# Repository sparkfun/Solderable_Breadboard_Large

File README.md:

#Solderable Breadboard Large
---

Solderable breadboard that mirrors a large (63 column) solderless board.

Includes provisions for screw terminal connectors, and an trace down the center gutter for ground.  Can be configured for up to 5 independent power rails.

[  
*Solderable Breadboard Large*](https://www.sparkfun.com/products/12699)

Design files for the [Solderable Breadboard Large](https://www.sparkfun.com/products/12699).

Repository Contents
-------------------

* **/Hardware** - Eagle PCB and schematic files

License Information
-------------------
The hardware is released under [Creative Commons ShareAlike 4.0 International](https://creativecommons.org/licenses/by-sa/4.0/).
The code is beerware; if you see me (or any other SparkFun employee) at the local, and you've found our code helpful, please buy us a round!

Distributed as-is; no warranty is given.

Author: Byron Jacquot @ SparkFun Electonics

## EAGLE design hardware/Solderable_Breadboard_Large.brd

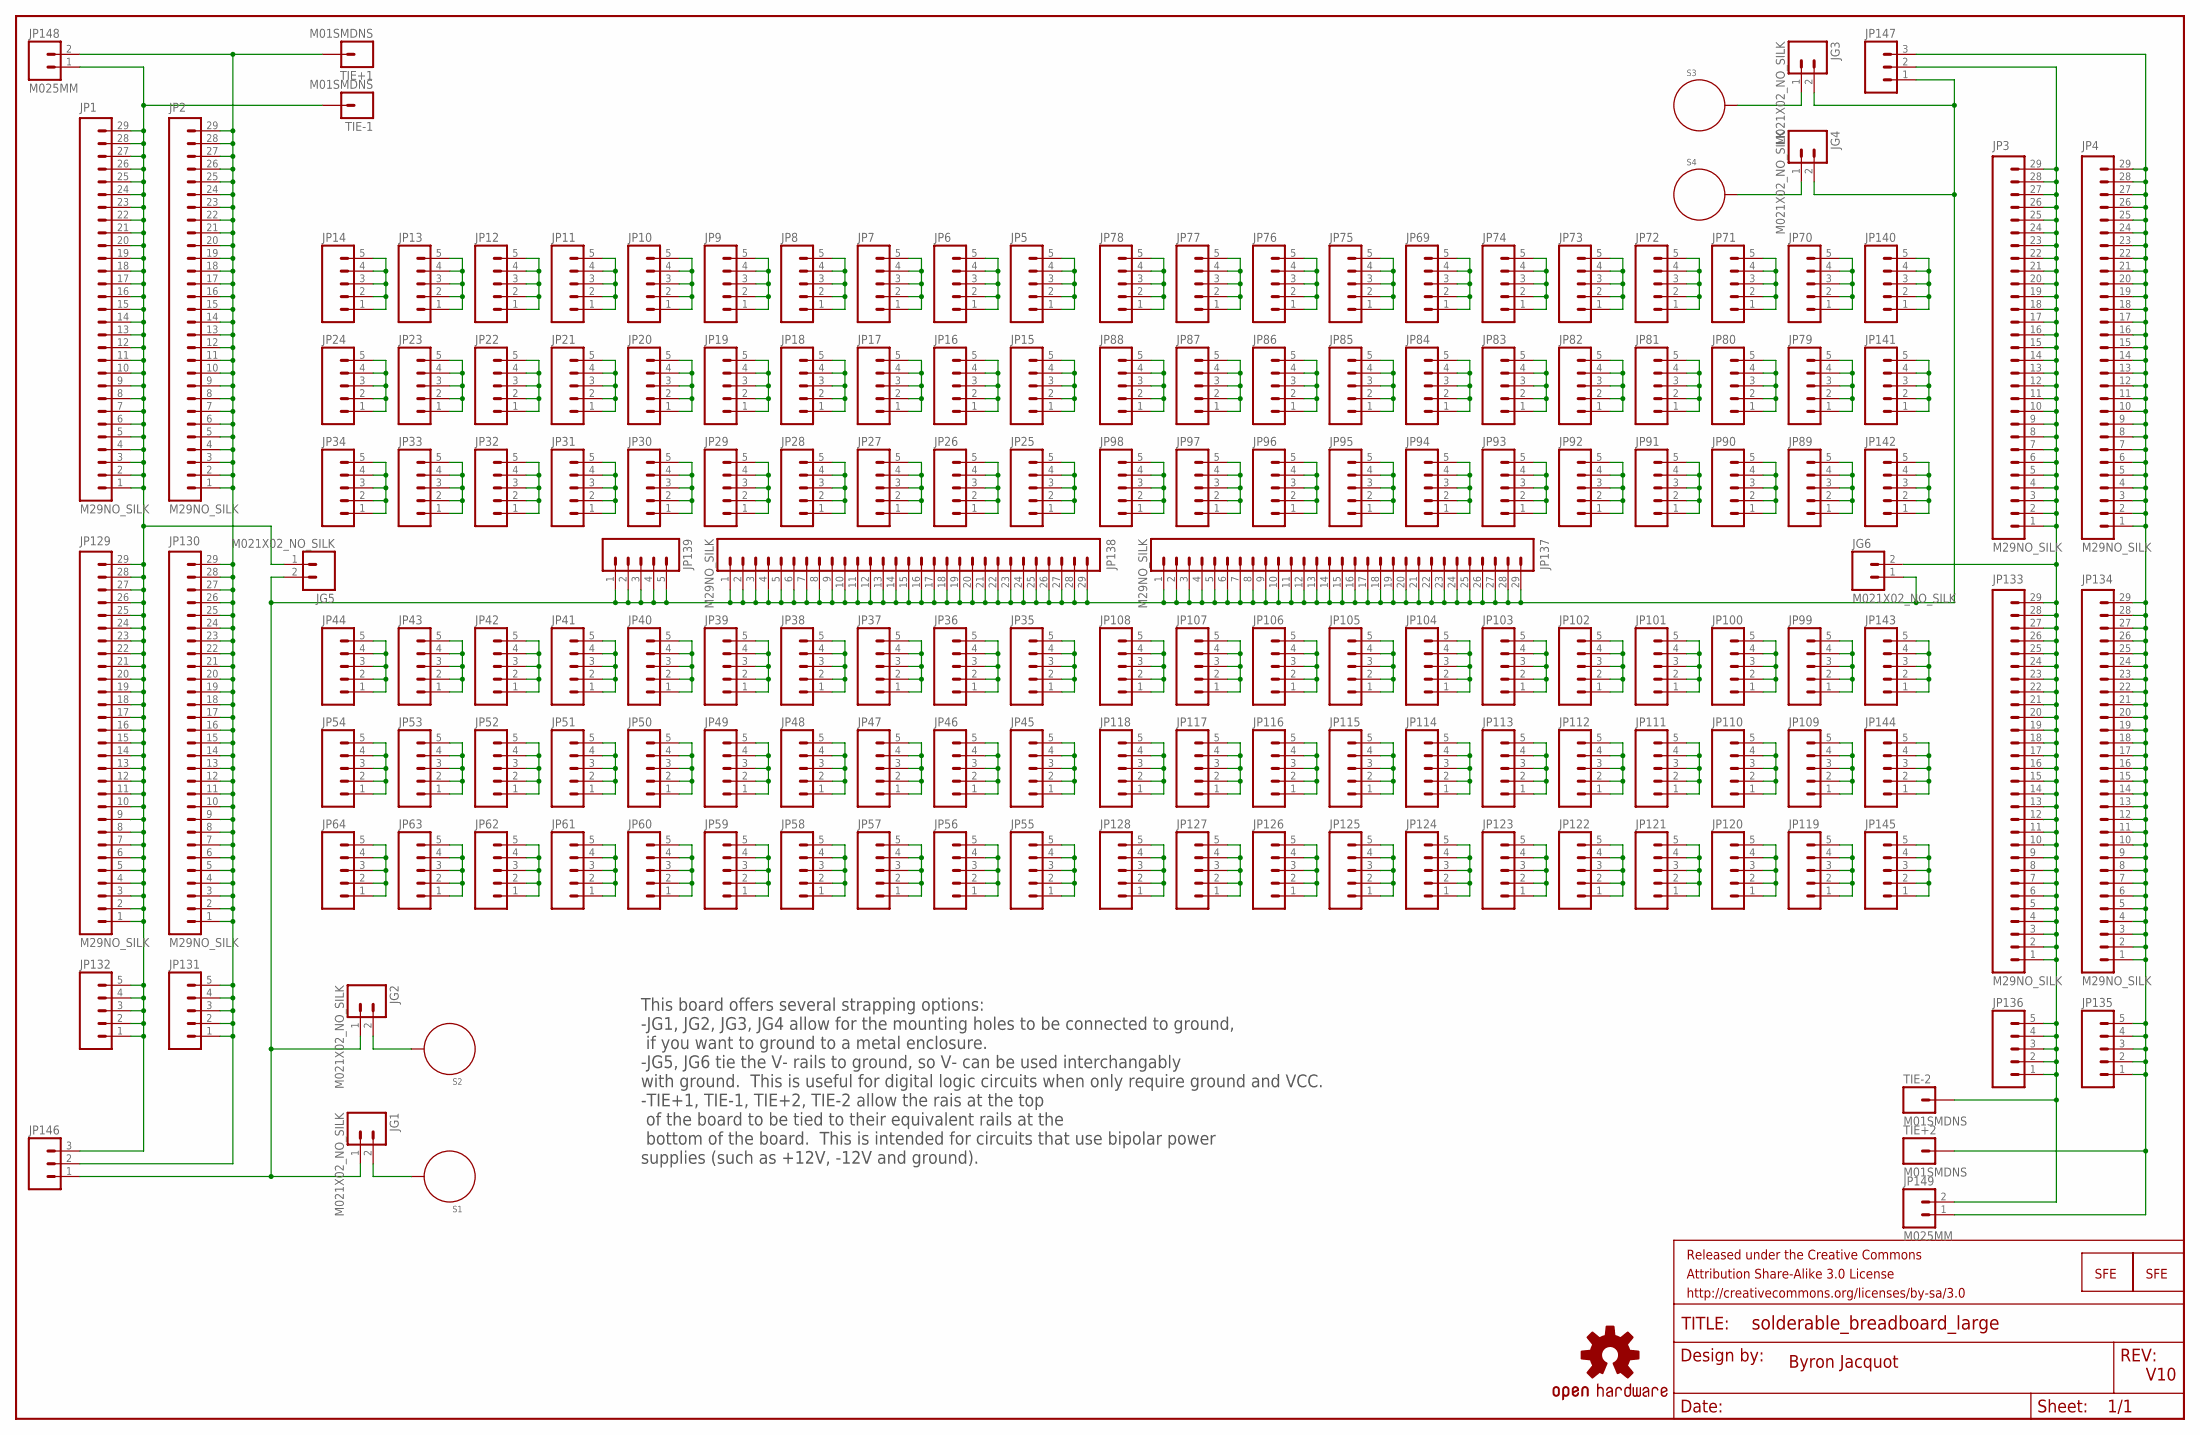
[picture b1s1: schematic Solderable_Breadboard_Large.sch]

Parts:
FRAME2: FRAME-LEDGER; CREATIVE_COMMONS
JG1, JG2, JG3, JG4, JG5, JG6: M021X02_NO_SILK; 1X02_NO_SILK
JP1, JP2, JP3, JP4, JP129, JP130, JP133, JP134, JP137, JP138: M29NO_SILK; 1X29_NO_SILK
JP5, JP6, JP7, JP8, JP9, JP10, JP11, JP12, JP13, JP14, JP15, JP16, JP17, JP18, JP19, JP20, JP21, JP22, JP23, JP24, JP25, JP26, JP27, JP28, JP29, JP30, JP31, JP32, JP33, JP34, JP35, JP36, JP37, JP38, JP39, JP40, JP41, JP42, JP43, JP44, JP45, JP46, JP47, JP48, JP49, JP50, JP51, JP52, JP53, JP54, JP55, JP56, JP57, JP58, JP59, JP60, JP61, JP62, JP63, JP64, JP69, JP70, JP71, JP72, JP73, JP74, JP75, JP76, JP77, JP78, JP79, JP80, JP81, JP82, JP83, JP84, JP85, JP86, JP87, JP88, JP89, JP90, JP91, JP92, JP93, JP94, JP95, JP96, JP97, JP98, JP99, JP100, JP101, JP102, JP103, JP104, JP105, JP106, JP107, JP108, JP109, JP110, JP111, JP112, JP113, JP114, JP115, JP116, JP117, JP118, JP119, JP120, JP121, JP122, JP123, JP124, JP125, JP126, JP127, JP128, JP131, JP132, JP135, JP136, JP139, JP140, JP141, JP142, JP143, JP144, JP145: M05NO_SILK; 1X05_NO_SILK
JP146, JP147: M03-SCREW-5MM; SCREWTERMINAL-5MM-3
JP148, JP149: M025MM; SCREWTERMINAL-5MM-2
LOGO1, LOGO2: LOGO-SFENEW; SFE-NEW-WEBLOGO
LOGO3: OSHW-LOGOS; OSHW-LOGO-S
S1, S2, S3, S4: STANDOFF_ELECTRICAL; STANDOFF-ELECTRICAL
TIE+1, TIE+2: M01SMDNS; 1X01NS
TIE-1, TIE-2: M01SMDNS; 1X01NS

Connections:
GND: JG1.1, JG2.1, JG3.2, JG4.2, JG5.2, JG6.1, JP137.1, JP137.2, JP137.3, JP137.4, JP137.5, JP137.6, JP137.7, JP137.8, JP137.9, JP137.10, JP137.11, JP137.12, JP137.13, JP137.14, JP137.15, JP137.16, JP137.17, JP137.18, JP137.19, JP137.20, JP137.21, JP137.22, JP137.23, JP137.24, JP137.25, JP137.26, JP137.27, JP137.28, JP137.29, JP138.1, JP138.2, JP138.3, JP138.4, JP138.5, JP138.6, JP138.7, JP138.8, JP138.9, JP138.10, JP138.11, JP138.12, JP138.13, JP138.14, JP138.15, JP138.16, JP138.17, JP138.18, JP138.19, JP138.20, JP138.21, JP138.22, JP138.23, JP138.24, JP138.25, JP138.26, JP138.27, JP138.28, JP138.29, JP139.1, JP139.2, JP139.3, JP139.4, JP139.5, JP146.1, JP147.1
unnamed: JG1.2, S1.P1
unnamed: JG2.2, S2.P1
unnamed: JP10.1, JP10.2, JP10.3, JP10.4, JP10.5
unnamed: JP5.1, JP5.2, JP5.3, JP5.4, JP5.5
unnamed: JP6.1, JP6.2, JP6.3, JP6.4, JP6.5
unnamed: JP7.1, JP7.2, JP7.3, JP7.4, JP7.5
unnamed: JP8.1, JP8.2, JP8.3, JP8.4, JP8.5
unnamed: JP9.1, JP9.2, JP9.3, JP9.4, JP9.5
unnamed: JP11.1, JP11.2, JP11.3, JP11.4, JP11.5
unnamed: JP12.1, JP12.2, JP12.3, JP12.4, JP12.5
unnamed: JP13.1, JP13.2, JP13.3, JP13.4, JP13.5
unnamed: JP14.1, JP14.2, JP14.3, JP14.4, JP14.5
unnamed: JP15.1, JP15.2, JP15.3, JP15.4, JP15.5
unnamed: JP16.1, JP16.2, JP16.3, JP16.4, JP16.5
unnamed: JP17.1, JP17.2, JP17.3, JP17.4, JP17.5
unnamed: JP18.1, JP18.2, JP18.3, JP18.4, JP18.5
unnamed: JP19.1, JP19.2, JP19.3, JP19.4, JP19.5
unnamed: JP20.1, JP20.2, JP20.3, JP20.4, JP20.5
unnamed: JP21.1, JP21.2, JP21.3, JP21.4, JP21.5
unnamed: JP22.1, JP22.2, JP22.3, JP22.4, JP22.5
unnamed: JP23.1, JP23.2, JP23.3, JP23.4, JP23.5
unnamed: JP24.1, JP24.2, JP24.3, JP24.4, JP24.5
unnamed: JP25.1, JP25.2, JP25.3, JP25.4, JP25.5
unnamed: JP26.1, JP26.2, JP26.3, JP26.4, JP26.5
unnamed: JP27.1, JP27.2, JP27.3, JP27.4, JP27.5
unnamed: JP28.1, JP28.2, JP28.3, JP28.4, JP28.5
unnamed: JP29.1, JP29.2, JP29.3, JP29.4, JP29.5
unnamed: JP30.1, JP30.2, JP30.3, JP30.4, JP30.5
unnamed: JP31.1, JP31.2, JP31.3, JP31.4, JP31.5
unnamed: JP32.1, JP32.2, JP32.3, JP32.4, JP32.5
unnamed: JP33.1, JP33.2, JP33.3, JP33.4, JP33.5
unnamed: JP34.1, JP34.2, JP34.3, JP34.4, JP34.5
unnamed: JP35.1, JP35.2, JP35.3, JP35.4, JP35.5
unnamed: JP36.1, JP36.2, JP36.3, JP36.4, JP36.5
unnamed: JP37.1, JP37.2, JP37.3, JP37.4, JP37.5
unnamed: JP38.1, JP38.2, JP38.3, JP38.4, JP38.5
unnamed: JP39.1, JP39.2, JP39.3, JP39.4, JP39.5
unnamed: JP40.1, JP40.2, JP40.3, JP40.4, JP40.5
unnamed: JP41.1, JP41.2, JP41.3, JP41.4, JP41.5
unnamed: JP42.1, JP42.2, JP42.3, JP42.4, JP42.5
unnamed: JP43.1, JP43.2, JP43.3, JP43.4, JP43.5
unnamed: JP44.1, JP44.2, JP44.3, JP44.4, JP44.5
unnamed: JP45.1, JP45.2, JP45.3, JP45.4, JP45.5
unnamed: JP46.1, JP46.2, JP46.3, JP46.4, JP46.5
unnamed: JP47.1, JP47.2, JP47.3, JP47.4, JP47.5
unnamed: JP48.1, JP48.2, JP48.3, JP48.4, JP48.5
unnamed: JP49.1, JP49.2, JP49.3, JP49.4, JP49.5
unnamed: JP50.1, JP50.2, JP50.3, JP50.4, JP50.5
unnamed: JP51.1, JP51.2, JP51.3, JP51.4, JP51.5
unnamed: JP52.1, JP52.2, JP52.3, JP52.4, JP52.5
unnamed: JP53.1, JP53.2, JP53.3, JP53.4, JP53.5
unnamed: JP54.1, JP54.2, JP54.3, JP54.4, JP54.5
unnamed: JP55.1, JP55.2, JP55.3, JP55.4, JP55.5
unnamed: JP56.1, JP56.2, JP56.3, JP56.4, JP56.5
unnamed: JP57.1, JP57.2, JP57.3, JP57.4, JP57.5
unnamed: JP58.1, JP58.2, JP58.3, JP58.4, JP58.5
unnamed: JP59.1, JP59.2, JP59.3, JP59.4, JP59.5
unnamed: JP60.1, JP60.2, JP60.3, JP60.4, JP60.5
unnamed: JP61.1, JP61.2, JP61.3, JP61.4, JP61.5
unnamed: JP62.1, JP62.2, JP62.3, JP62.4, JP62.5
unnamed: JP63.1, JP63.2, JP63.3, JP63.4, JP63.5
unnamed: JP64.1, JP64.2, JP64.3, JP64.4, JP64.5
unnamed: JG3.1, S3.P1
unnamed: JG4.1, S4.P1
unnamed: JP69.1, JP69.2, JP69.3, JP69.4, JP69.5
unnamed: JP70.1, JP70.2, JP70.3, JP70.4, JP70.5
unnamed: JP71.1, JP71.2, JP71.3, JP71.4, JP71.5
unnamed: JP72.1, JP72.2, JP72.3, JP72.4, JP72.5
unnamed: JP73.1, JP73.2, JP73.3, JP73.4, JP73.5
unnamed: JP74.1, JP74.2, JP74.3, JP74.4, JP74.5
unnamed: JP75.1, JP75.2, JP75.3, JP75.4, JP75.5
unnamed: JP76.1, JP76.2, JP76.3, JP76.4, JP76.5
unnamed: JP77.1, JP77.2, JP77.3, JP77.4, JP77.5
unnamed: JP78.1, JP78.2, JP78.3, JP78.4, JP78.5
unnamed: JP79.1, JP79.2, JP79.3, JP79.4, JP79.5
unnamed: JP80.1, JP80.2, JP80.3, JP80.4, JP80.5
unnamed: JP81.1, JP81.2, JP81.3, JP81.4, JP81.5
unnamed: JP82.1, JP82.2, JP82.3, JP82.4, JP82.5
unnamed: JP83.1, JP83.2, JP83.3, JP83.4, JP83.5
unnamed: JP84.1, JP84.2, JP84.3, JP84.4, JP84.5
unnamed: JP85.1, JP85.2, JP85.3, JP85.4, JP85.5
unnamed: JP86.1, JP86.2, JP86.3, JP86.4, JP86.5
unnamed: JP87.1, JP87.2, JP87.3, JP87.4, JP87.5
unnamed: JP88.1, JP88.2, JP88.3, JP88.4, JP88.5
unnamed: JP89.1, JP89.2, JP89.3, JP89.4, JP89.5
unnamed: JP90.1, JP90.2, JP90.3, JP90.4, JP90.5
unnamed: JP91.1, JP91.2, JP91.3, JP91.4, JP91.5
unnamed: JP92.1, JP92.2, JP92.3, JP92.4, JP92.5
unnamed: JP93.1, JP93.2, JP93.3, JP93.4, JP93.5
unnamed: JP94.1, JP94.2, JP94.3, JP94.4, JP94.5
unnamed: JP95.1, JP95.2, JP95.3, JP95.4, JP95.5
unnamed: JP96.1, JP96.2, JP96.3, JP96.4, JP96.5
unnamed: JP97.1, JP97.2, JP97.3, JP97.4, JP97.5
unnamed: JP98.1, JP98.2, JP98.3, JP98.4, JP98.5
unnamed: JP99.1, JP99.2, JP99.3, JP99.4, JP99.5
unnamed: JP100.1, JP100.2, JP100.3, JP100.4, JP100.5
unnamed: JP101.1, JP101.2, JP101.3, JP101.4, JP101.5
unnamed: JP102.1, JP102.2, JP102.3, JP102.4, JP102.5
unnamed: JP103.1, JP103.2, JP103.3, JP103.4, JP103.5
unnamed: JP104.1, JP104.2, JP104.3, JP104.4, JP104.5
unnamed: JP105.1, JP105.2, JP105.3, JP105.4, JP105.5
unnamed: JP106.1, JP106.2, JP106.3, JP106.4, JP106.5
unnamed: JP107.1, JP107.2, JP107.3, JP107.4, JP107.5
unnamed: JP108.1, JP108.2, JP108.3, JP108.4, JP108.5
unnamed: JP109.1, JP109.2, JP109.3, JP109.4, JP109.5
unnamed: JP110.1, JP110.2, JP110.3, JP110.4, JP110.5
unnamed: JP111.1, JP111.2, JP111.3, JP111.4, JP111.5
unnamed: JP112.1, JP112.2, JP112.3, JP112.4, JP112.5
unnamed: JP113.1, JP113.2, JP113.3, JP113.4, JP113.5
unnamed: JP114.1, JP114.2, JP114.3, JP114.4, JP114.5
unnamed: JP115.1, JP115.2, JP115.3, JP115.4, JP115.5
unnamed: JP116.1, JP116.2, JP116.3, JP116.4, JP116.5
unnamed: JP117.1, JP117.2, JP117.3, JP117.4, JP117.5
unnamed: JP118.1, JP118.2, JP118.3, JP118.4, JP118.5
unnamed: JP119.1, JP119.2, JP119.3, JP119.4, JP119.5
unnamed: JP120.1, JP120.2, JP120.3, JP120.4, JP120.5
unnamed: JP121.1, JP121.2, JP121.3, JP121.4, JP121.5
unnamed: JP122.1, JP122.2, JP122.3, JP122.4, JP122.5
unnamed: JP123.1, JP123.2, JP123.3, JP123.4, JP123.5
unnamed: JP124.1, JP124.2, JP124.3, JP124.4, JP124.5
unnamed: JP125.1, JP125.2, JP125.3, JP125.4, JP125.5
unnamed: JP126.1, JP126.2, JP126.3, JP126.4, JP126.5
unnamed: JP127.1, JP127.2, JP127.3, JP127.4, JP127.5
unnamed: JP128.1, JP128.2, JP128.3, JP128.4, JP128.5
unnamed: JP140.1, JP140.2, JP140.3, JP140.4, JP140.5
unnamed: JP141.1, JP141.2, JP141.3, JP141.4, JP141.5
unnamed: JP142.1, JP142.2, JP142.3, JP142.4, JP142.5
unnamed: JP143.1, JP143.2, JP143.3, JP143.4, JP143.5
unnamed: JP144.1, JP144.2, JP144.3, JP144.4, JP144.5
unnamed: JP145.1, JP145.2, JP145.3, JP145.4, JP145.5
V+BOT: JP4.1, JP4.2, JP4.3, JP4.4, JP4.5, JP4.6, JP4.7, JP4.8, JP4.9, JP4.10, JP4.11, JP4.12, JP4.13, JP4.14, JP4.15, JP4.16, JP4.17, JP4.18, JP4.19, JP4.20, JP4.21, JP4.22, JP4.23, JP4.24, JP4.25, JP4.26, JP4.27, JP4.28, JP4.29, JP134.1, JP134.2, JP134.3, JP134.4, JP134.5, JP134.6, JP134.7, JP134.8, JP134.9, JP134.10, JP134.11, JP134.12, JP134.13, JP134.14, JP134.15, JP134.16, JP134.17, JP134.18, JP134.19, JP134.20, JP134.21, JP134.22, JP134.23, JP134.24, JP134.25, JP134.26, JP134.27, JP134.28, JP134.29, JP135.1, JP135.2, JP135.3, JP135.4, JP135.5, JP147.3, JP149.1, TIE+2.1
V+TOP: JP2.1, JP2.2, JP2.3, JP2.4, JP2.5, JP2.6, JP2.7, JP2.8, JP2.9, JP2.10, JP2.11, JP2.12, JP2.13, JP2.14, JP2.15, JP2.16, JP2.17, JP2.18, JP2.19, JP2.20, JP2.21, JP2.22, JP2.23, JP2.24, JP2.25, JP2.26, JP2.27, JP2.28, JP2.29, JP130.1, JP130.2, JP130.3, JP130.4, JP130.5, JP130.6, JP130.7, JP130.8, JP130.9, JP130.10, JP130.11, JP130.12, JP130.13, JP130.14, JP130.15, JP130.16, JP130.17, JP130.18, JP130.19, JP130.20, JP130.21, JP130.22, JP130.23, JP130.24, JP130.25, JP130.26, JP130.27, JP130.28, JP130.29, JP131.1, JP131.2, JP131.3, JP131.4, JP131.5, JP146.2, JP148.2, TIE+1.1
V-BOT: JG6.2, JP3.1, JP3.2, JP3.3, JP3.4, JP3.5, JP3.6, JP3.7, JP3.8, JP3.9, JP3.10, JP3.11, JP3.12, JP3.13, JP3.14, JP3.15, JP3.16, JP3.17, JP3.18, JP3.19, JP3.20, JP3.21, JP3.22, JP3.23, JP3.24, JP3.25, JP3.26, JP3.27, JP3.28, JP3.29, JP133.1, JP133.2, JP133.3, JP133.4, JP133.5, JP133.6, JP133.7, JP133.8, JP133.9, JP133.10, JP133.11, JP133.12, JP133.13, JP133.14, JP133.15, JP133.16, JP133.17, JP133.18, JP133.19, JP133.20, JP133.21, JP133.22, JP133.23, JP133.24, JP133.25, JP133.26, JP133.27, JP133.28, JP133.29, JP136.1, JP136.2, JP136.3, JP136.4, JP136.5, JP147.2, JP149.2, TIE-2.1
V-TOP: JG5.1, JP1.1, JP1.2, JP1.3, JP1.4, JP1.5, JP1.6, JP1.7, JP1.8, JP1.9, JP1.10, JP1.11, JP1.12, JP1.13, JP1.14, JP1.15, JP1.16, JP1.17, JP1.18, JP1.19, JP1.20, JP1.21, JP1.22, JP1.23, JP1.24, JP1.25, JP1.26, JP1.27, JP1.28, JP1.29, JP129.1, JP129.2, JP129.3, JP129.4, JP129.5, JP129.6, JP129.7, JP129.8, JP129.9, JP129.10, JP129.11, JP129.12, JP129.13, JP129.14, JP129.15, JP129.16, JP129.17, JP129.18, JP129.19, JP129.20, JP129.21, JP129.22, JP129.23, JP129.24, JP129.25, JP129.26, JP129.27, JP129.28, JP129.29, JP132.1, JP132.2, JP132.3, JP132.4, JP132.5, JP146.3, JP148.1, TIE-1.1

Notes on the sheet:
Byron Jacquot
V10
This board offers several strapping options: -JG1, JG2, JG3, JG4 allow for the mounting holes to be connected to ground, if you want to ground to a metal enclosure. -JG5, JG6 tie the V- rails to ground, so V- can be used interchangably with ground. This is useful for digital logic circuits when onl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

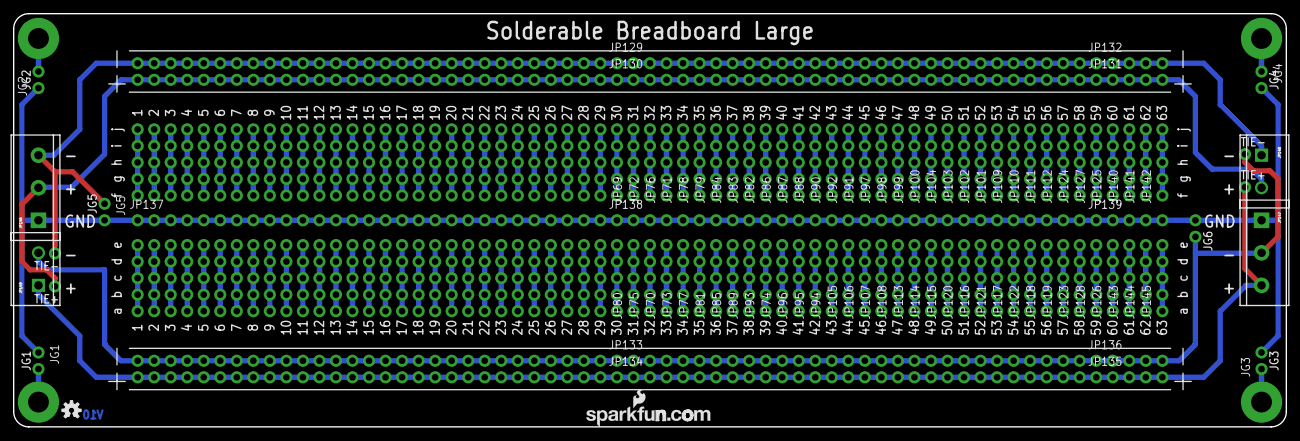
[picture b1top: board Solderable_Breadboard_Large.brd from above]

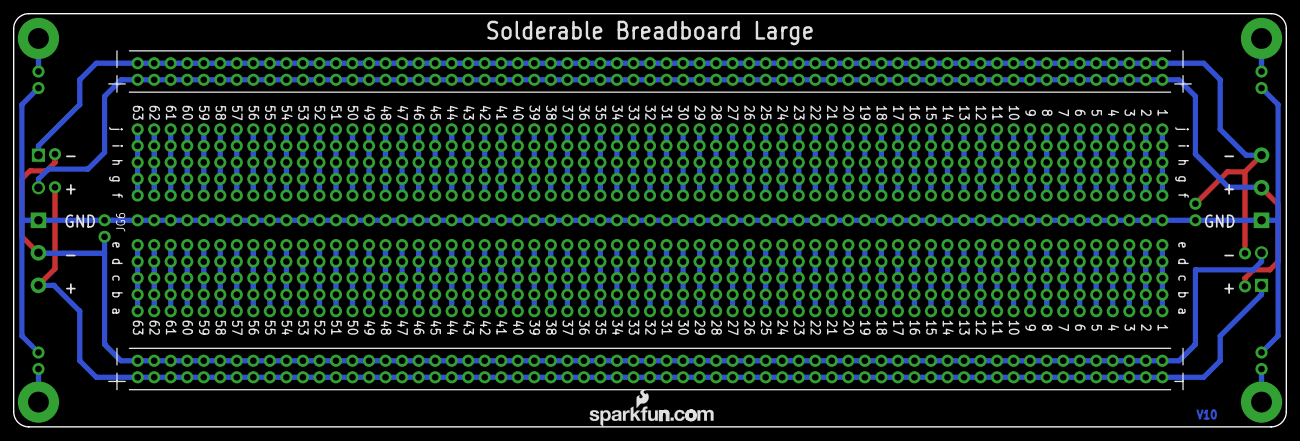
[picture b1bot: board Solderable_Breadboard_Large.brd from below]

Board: 2 copper layers, 195.6 x 63.5 mm, 163 parts (2 on the bottom side), 135 nets.

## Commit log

2013-11-27 Initial commit - readme & .gitignore
2013-11-27 Initial PCB files.
2014-01-03 Update README.md
    Renaming repo
2014-01-06 Revision after group review.
    -Changes to naming/branding.
    -Added extra jumper option for 2-rails only operation.
2014-01-14 Renamed files to match product name, and updates from reviewing protos.
2014-01-14 Ready for reds
    A little more cleanup.
2014-02-20 Updating README.md
2014-02-20 Fixing readme formatting

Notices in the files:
parts and their libraries:
SparkFun-Aesthetics: Licensing: CC v3.0 Share-Alike You are welcome to use this library for commercial purposes.
SparkFun-Aesthetics: Released under the Creative Commons Attribution Share-Alike 3.0 License
SparkFun-Aesthetics: http://creativecommons.org/licenses/by-sa/3.0
